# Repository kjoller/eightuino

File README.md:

eightuino
=========

Yet another arduino-like board, with the benefits of having a sane 2.54mm pin spacing. Also have the advantage of being a through-hole design, making it perfect for a beginner soldering project.

It is also cheap to build, as the board is less than the 5x5cm size required for the lowest price tier at several chinese prototyping serivces (IteadStudio, SeeedStudio, Elecrow).

The distance between the two rows of headers (17 mil) makes it suited for 5cm wide protoboards (which come very cheaply, as opposed to 'real' arduino proto-shields).

The project sprang out of a wish to improve my very first project, the [Cheapuino]

[Cheapuino]: http://lab.kjlr.dk/p/cheapuino

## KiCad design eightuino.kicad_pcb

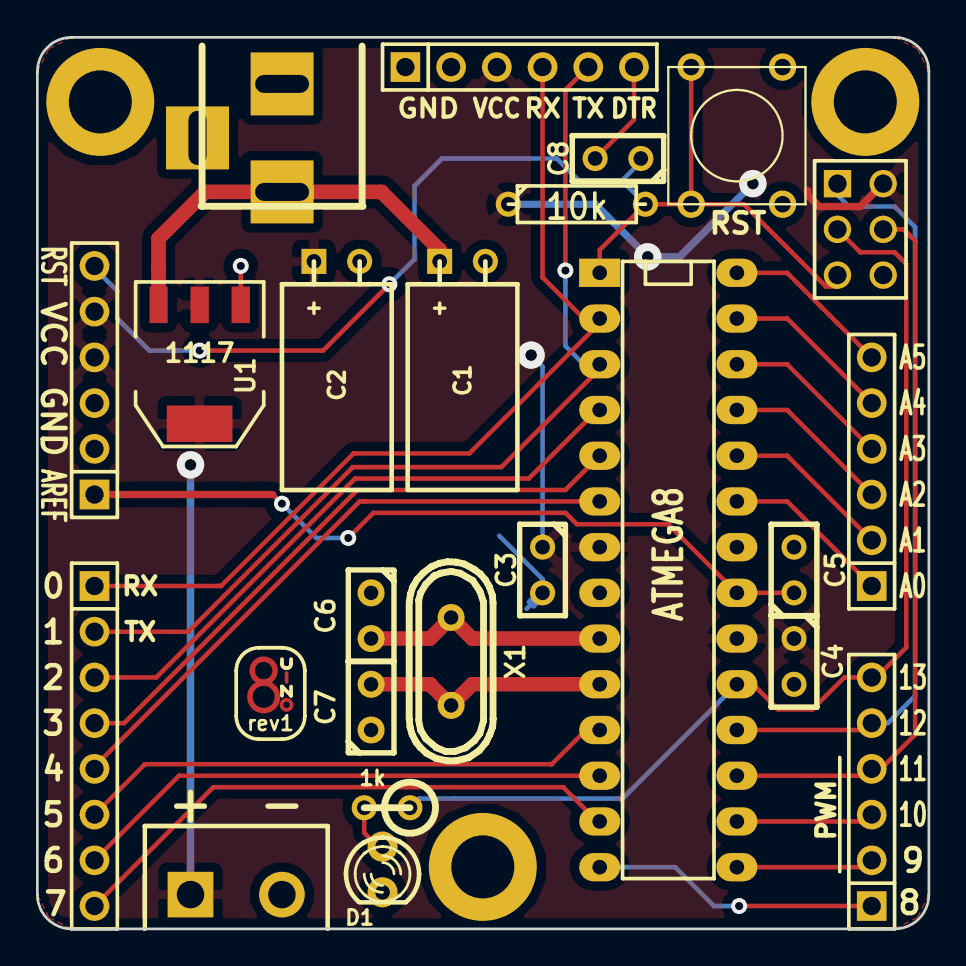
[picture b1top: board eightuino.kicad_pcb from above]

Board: 2 copper layers, 49.5 x 49.5 mm, 28 parts (1 on the bottom side), 29 nets.

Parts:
1PIN, 1PIN#2, 1PIN#3: P***; 1pin
8uino2: rev1; 8uino_mix_silk+mask+copper
BT1: Unregulated Battery; bornier2
C1, C2: CP1; C1V5H
C3, C4, C5, C8: 100nF; C1
C6, C7: 22pF; cnp_3mm_disc
CON1: BARREL_JACK
D1: LED; LED-3MM
IC1: ATMEGA8; DIP-28__300_ELL
P1: PowerPins; Pinrow_6p
P2: Analog; Pinrow_6p
P3: Digital1; Pinrow_8p
P4: Digital_2; Pinrow_6p
P5: Serial; Pinrow_6p
P6: ISP; pin_array_3x2
R1: 10k; R3
R2: 1k; R1
SW1: RST; SW_PUSH_SMALL
SYM: Symbol_OSHW-Logo_SilkScreen_07Jul2012
U1: 1117; SOT223
X1: CRYSTAL; Crystal_HC49-U_Vertical_RevA_09Aug2010

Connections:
/DTR: C8.2, P5.6
/MISO: IC1.18, P4.5, P6.1
/MOSI: IC1.17, P4.4, P6.4
/RST: C8.1, IC1.1, P1.6, P6.5, R1.2, SW1.2
/RX: IC1.2, P3.1, P5.4
/SCK: IC1.19, P4.6, P6.3, R2.1
/TX: IC1.3, P3.2, P5.5
/XTAL1: C6.2, IC1.9, X1.2
/XTAL2: C7.2, IC1.10, X1.1
GND: 1PIN.1, 1PIN#2.1, 1PIN#3.1, BT1.2, C1.2, C2.2, C3.2, C4.2, C5.2, C6.1, C7.1, CON1.2, CON1.3, D1.2, IC1.8, IC1.22, P1.2, P1.3, P5.1, P5.2, P6.6, SW1.1, U1.1
unnamed: C1.1, CON1.1, U1.3
unnamed: C5.1, IC1.21, P1.1
unnamed: D1.1, R2.2
unnamed: IC1.4, P3.3
unnamed: IC1.5, P3.4
unnamed: IC1.6, P3.5
unnamed: IC1.11, P3.6
unnamed: IC1.12, P3.7
unnamed: IC1.13, P3.8
unnamed: IC1.14, P4.1
unnamed: IC1.15, P4.2
unnamed: IC1.16, P4.3
unnamed: IC1.23, P2.1
unnamed: IC1.24, P2.2
unnamed: IC1.25, P2.3
unnamed: IC1.26, P2.4
unnamed: IC1.27, P2.5
unnamed: IC1.28, P2.6
VCC: BT1.1, C2.1, C3.1, C4.1, IC1.7, IC1.20, P1.4, P1.5, P5.3, P6.2, R1.1, U1.2, U1.4

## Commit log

2014-01-14 Update LICENSE
2014-01-14 Initial commit of project files
2014-01-14 Added FTDI connector in schematic
2014-01-15 Changed schematic to 6-pin ISP
2014-01-16 Almost total board rework.
2014-01-16 Change to the logo module
2014-01-16 Remembered to save schematic
2014-01-24 Changed to tfqp32 package and added ADC6 and ADC7
2014-01-24 Updated netlist and components to SMD
2014-01-25 Components mostly laid out, tracks still missing
2014-01-25 Removed a rogue + and -
2014-01-26 Added LC filter at AVCC, cleaned schematic up a bit

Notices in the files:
eightuino.kicad_pcb:
© 2013 Niels Kjøller Hansen
